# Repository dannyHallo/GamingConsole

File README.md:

# GamingConsole
 Hipster Game Console

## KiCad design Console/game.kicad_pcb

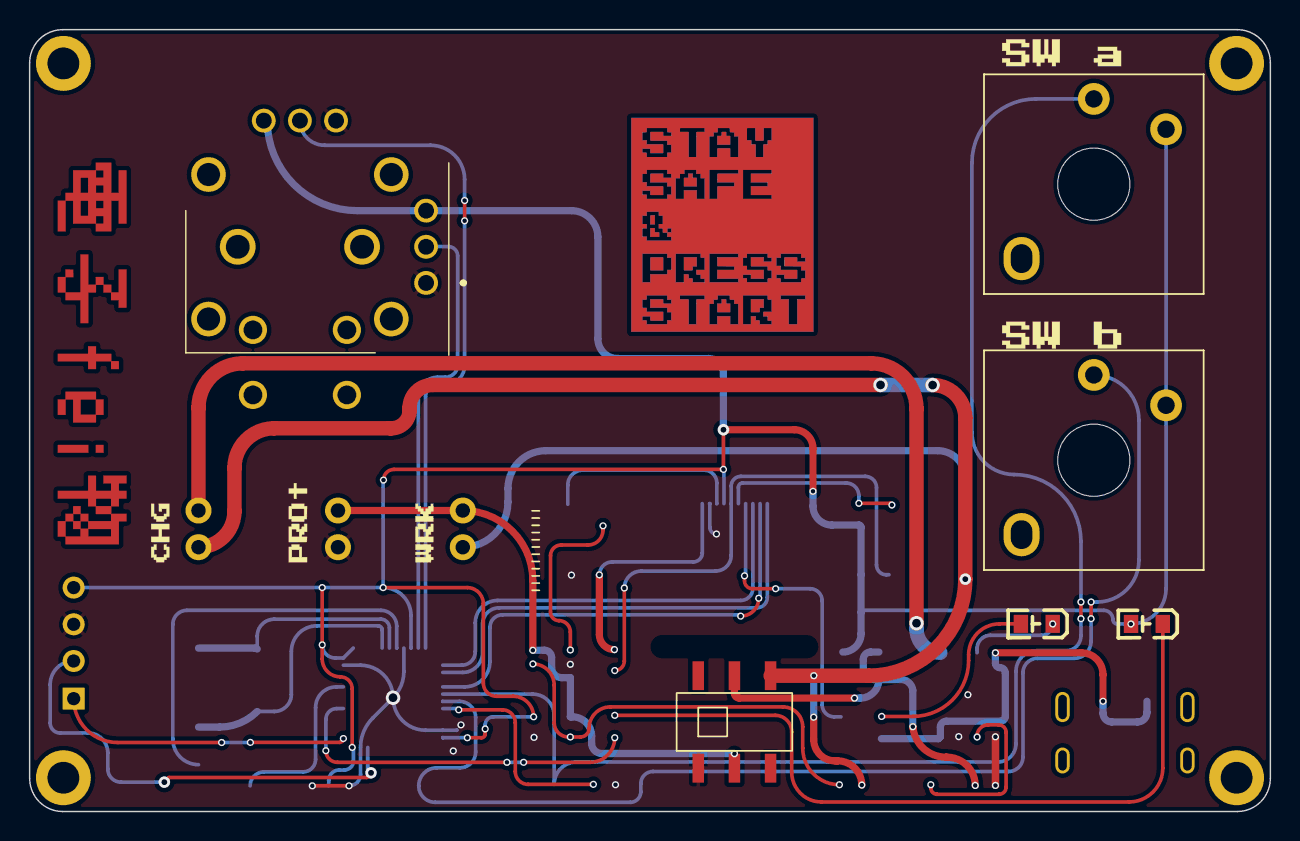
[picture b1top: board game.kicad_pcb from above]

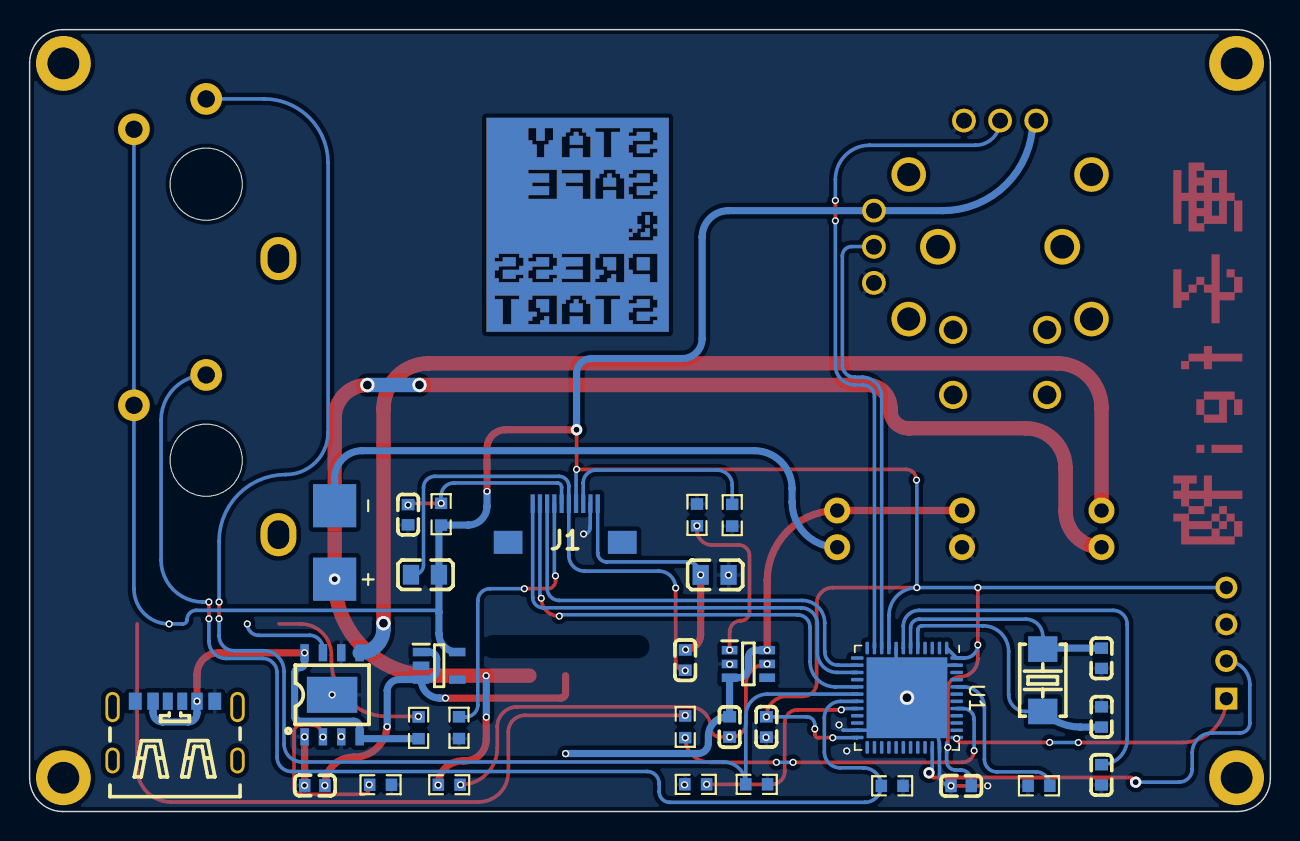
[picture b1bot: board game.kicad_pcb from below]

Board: 2 copper layers, 85.9 x 54.1 mm, 46 parts (32 on the bottom side), 34 nets.

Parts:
B1: Li-ion_600maH_1A; 2P bat
C1, C7: 0.1uF; C0603
C2, C4, C6, C8: 1uF; C0603
C3, C9: 20pF; C0603
C5: 10uF; C0603
FB1, FB2: FB0805; L0805
IC1: ADP160AUJZ-3.3-R7; SOT95P280X100-5N
IC2: DW07D; SOT95P290X124-6N
IC3: TP4056X; ESOP-8_L4.9-W3.9-P1.27-LS6.0-BL-EP
J1: FPC 0.5mm 10P
J2: TYPE-C-31-M-17; TYPE-C-SMD_TYPE-C-31-M-16
JP1: Charge current; Jumper_2P
JP2: Working current; Jumper_2P
JP3: Short Bat Protection; Jumper_2P
LED1, LED2: Led; LED0805-RD_RED
Mt**: Copy_MountingHole_2.2mm_M2_DIN965_Pad
Mt**#2, Mt**#3, Mt**#4: Copy_MountingHole_2.2mm_M2_DIN965_Pad
P1: SWDPins; 4X1_PROGRAM_PIN
R1, R2, R6, R7, R10, R11, R12: 10k; R0603
R3, R5, R8, R9: 1k; R0603
R4: 1.1k; R0603
Ref**: Val**; gaming_101
S1: RKJXV122400R
S2, S3: PG1353; SW_Kailh_Choc_V2
S4: 9*3.5*3.5_toggle_switch; 9_3.5_3.5_Toggle_Switch
U1: STM32F103CBUx; QFN-48-1EP_7x7mm_P0.5mm_EP5.6x5.6mm
Y1: 5032/2P; 5032_2P

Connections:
/3V3: C6.1, C8.1, FB1.1, IC1.5 (VOUT), J1.7, LED1.2 (A), P1.1 (3V3), R1.2, S1.A13, S1.B13, S2.2, S3.2, U1.1 (VBAT), U1.9 (VDDA), U1.24 (VDD), U1.36 (VDD), U1.48 (VDD)
/ADC_IN0: S1.A12, U1.10 (PA0)
/ADC_IN1: S1.B12, U1.11 (PA1)
/AGND: C2.2, FB2.2, J1.10
/AVDD: C2.1, FB1.2, J1.6
/CS: J1.3, U1.14 (PA4)
/ChargeIn: IC3.4 (VCC), IC3.8 (CE), J2.A9 (VBUS_1), J2.B9 (VBUS_2), R5.2
/DISP: C1.1, J1.5, R1.1
/EXTCOMM: J1.4, R6.1
/EXTMODE: J1.8, R2.1
/GND: C1.2, C3.1, C4.2, C6.2, C7.1, C8.2, C9.1, FB2.1, IC1.2 (GND), IC2.2 (S1), IC3.1 (TEMP), IC3.3 (GND), IC3.6 (~STDBY), IC3.9 (EAD), J1.9, J2.A12 (GND_1), J2.B12 (GND_2), JP3.2, P1.2 (GND), R2.2, R3.1, R4.1, R6.2, R7.1, R10.2, R11.1, R12.2, S1.A11, S1.B11, S4.1, U1.8 (VSSA), U1.23 (VSS), U1.35 (VSS), U1.47 (VSS), U1.49 (VSS)
/MOSI: J1.2, U1.17 (PA7)
/NRST: C7.2, U1.7 (NRST)
/PB0: R10.1, S2.1, U1.18 (PB0)
/PB1: R12.1, S3.1, U1.19 (PB1)
/PD0: C9.2, U1.5 (PD0), Y1.1
/PD1: C3.2, U1.6 (PD1), Y1.2
/S2: C5.2, IC2.3 (S2), IC2.6 (VSS), JP2.1, JP3.1, S4.2
/SCK: J1.1, U1.15 (PA5)
/SWCLK: P1.4 (SWCLK), U1.37 (PA14)
/SWDIO: P1.3 (SWDIO), U1.34 (PA13)
/Vbat: B1.2, JP1.1, R9.2, S4.4
/Vin: C4.1, IC1.1 (VIN), IC1.3 (EN), S4.5
unnamed: B1.1, JP2.2
unnamed: C5.1, IC2.5 (VDD), R9.1
unnamed: IC2.1 (V-), R3.2
unnamed: IC3.2 (PROG), R4.2
unnamed: IC3.5 (BAT), JP1.2
unnamed: IC3.7 (~CHRG), LED2.1 (K)
unnamed: LED2.2 (A), R5.1
unnamed: LED1.1 (K), R8.1
unnamed: R11.2, U1.44 (BOOT0)
unnamed: R8.2, U1.41 (PB5)
unnamed: R7.2, U1.20 (PB2)
